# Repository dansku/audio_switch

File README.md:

# Audio Switch PCB 

A simple electronics project developed using EagleCad to switch two audio sources.

**Full blog post for the project https://www.danielandrade.net/2016/04/10/build-a-3-5mm-audio-switch/**

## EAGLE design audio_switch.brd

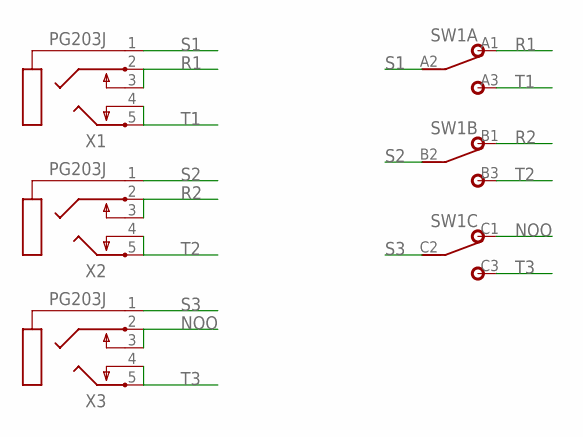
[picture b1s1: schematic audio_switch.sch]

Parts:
SW1: 3PDT
X1, X2, X3: PG203J

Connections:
NOO: SW1.C1 (1), X3.2, X3.3
R1: SW1.A1 (1), X1.2, X1.3
R2: SW1.B1 (1), X2.2, X2.3
S1: SW1.A2 (2), X1.1
S2: SW1.B2 (2), X2.1
S3: SW1.C2 (2), X3.1
T1: SW1.A3 (3), X1.4, X1.5
T2: SW1.B3 (3), X2.4, X2.5
T3: SW1.C3 (3), X3.4, X3.5

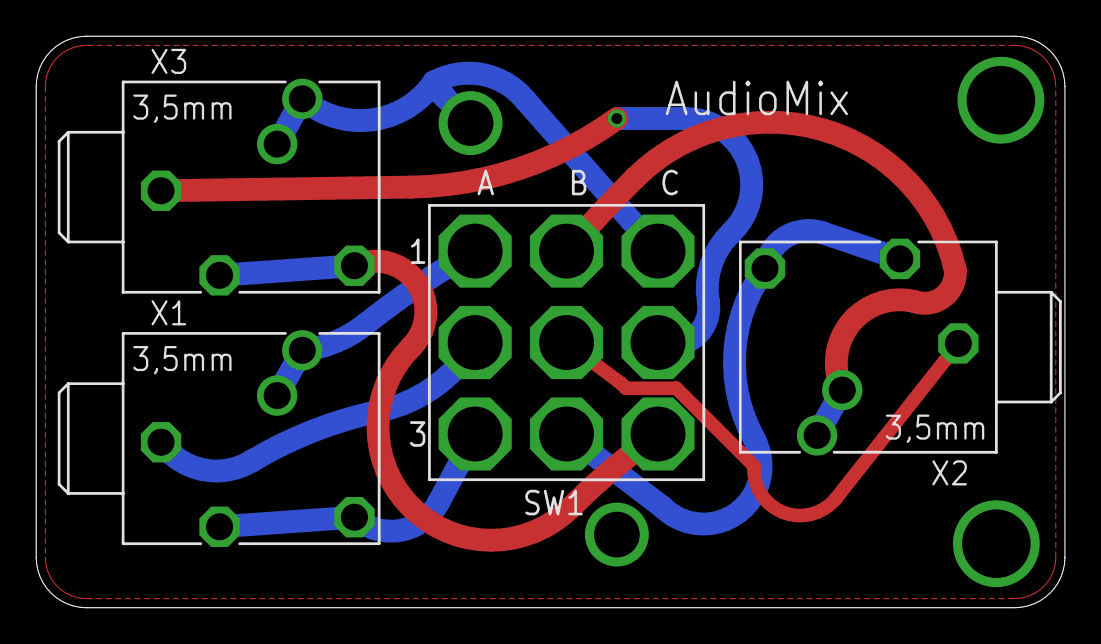
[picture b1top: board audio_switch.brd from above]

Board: 2 copper layers, 57.1 x 31.8 mm, 4 parts (0 on the bottom side), 9 nets.

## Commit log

2016-04-10 Initial commit :)
2016-04-10 Add pics.
2017-07-24 update to https
